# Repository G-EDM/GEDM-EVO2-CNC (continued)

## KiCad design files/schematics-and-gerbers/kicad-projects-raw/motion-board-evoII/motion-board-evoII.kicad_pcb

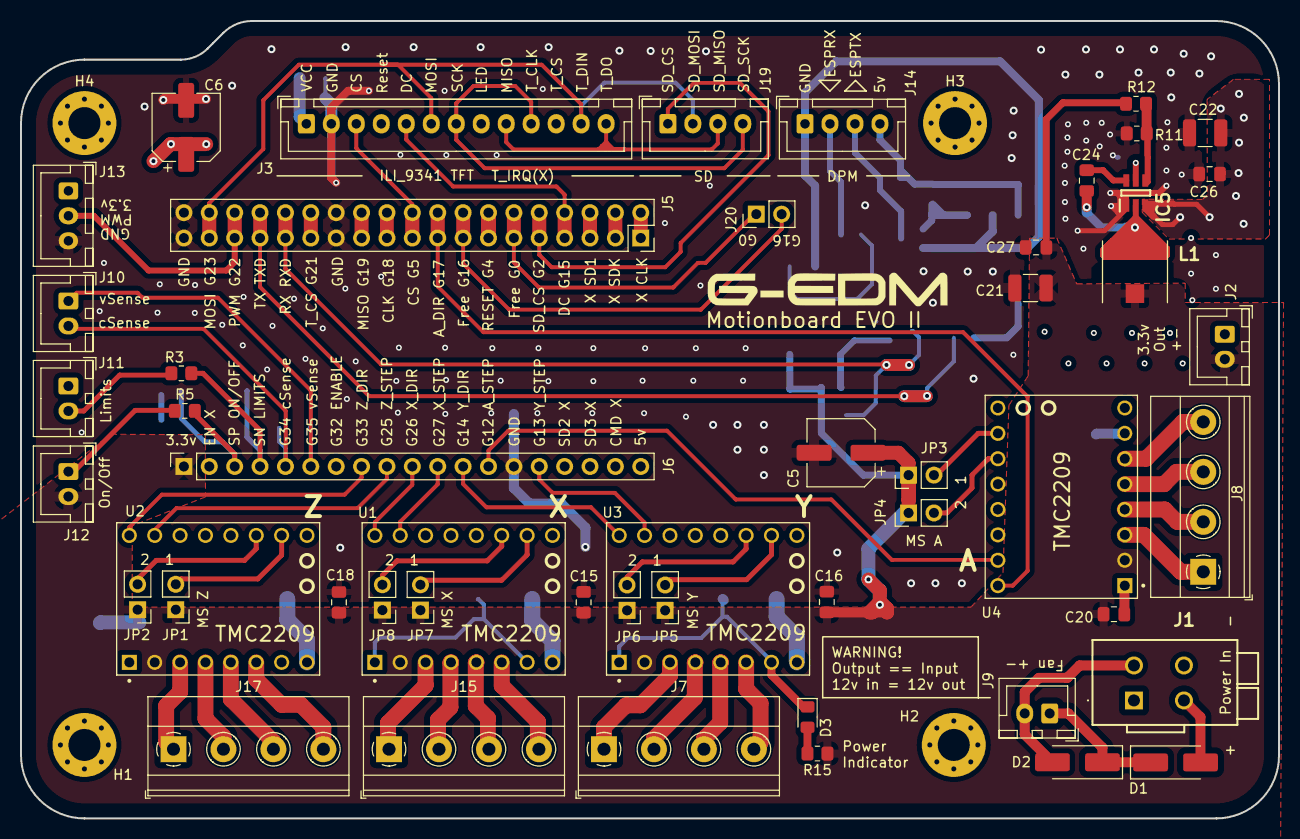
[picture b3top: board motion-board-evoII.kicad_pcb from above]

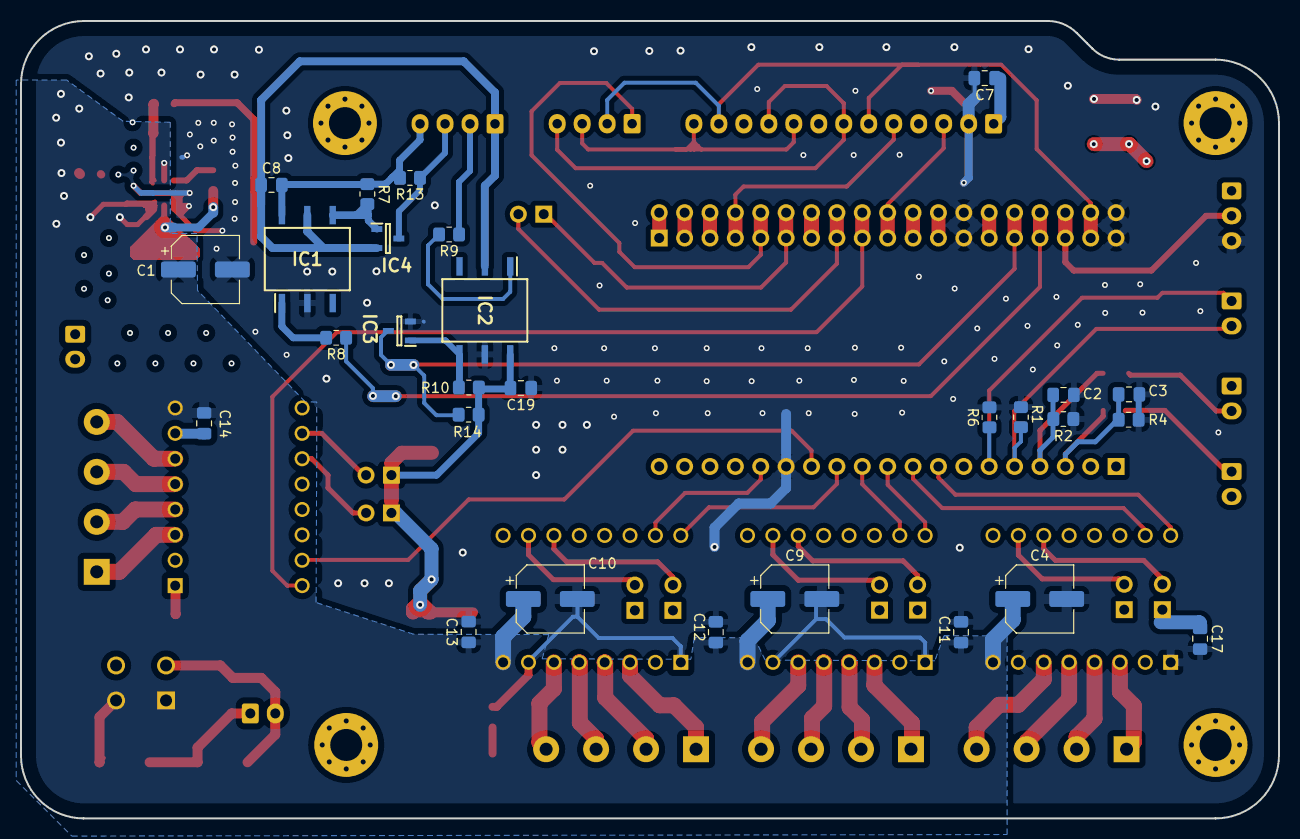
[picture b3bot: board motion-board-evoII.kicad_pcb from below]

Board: 4 copper layers, 125.9 x 79.8 mm, 82 parts (28 on the bottom side), 71 nets.

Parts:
C1, C4, C9, C10: 100uf35v-6.3x7.7mm (EEE-HA1V101XP); CP_Elec_6.3x7.7
C2, C3, C7, C8, C11, C12, C13, C14, C15, C16, C17, C18, C19, C20, C24, C26, C27: 0.1uf-50v-x7r; C_0805_2012Metric_Pad1.18x1.45mm_HandSolder
C5, C6: 220uf16v-6.3x7.7mm (EEE-HA1C221XP); CP_Elec_6.3x7.7
C21: 22uf-16v-X7R (GRM32ER71C226KEA8K); C_1210_3225Metric_Pad1.33x2.70mm_HandSolder
C22: 4.7uf-50v-X7R (GRM32ER71H475KA88L); C_1210_3225Metric_Pad1.33x2.70mm_HandSolder
D1, D2: 60v3ASchottky; D_SMA_Handsoldering
D3: 597-3305-607F; LED_0805_2012Metric_Pad1.15x1.40mm_HandSolder
H1: MountingHole_Pad; MountingHole_3.2mm_M3_Pad_Via
H2, H3, H4: MountingHole; MountingHole_3.2mm_M3_Pad_Via
IC1, IC2: H11L1SR2M_F132; SOT254P916X480-6N
IC3, IC4: MMBT3904; SOT95P240X110-3N
IC5: LMR51420XFDDCR; SOT95P280X110-6N
J1: WAGO 2601-1102; 26011102
J2, J9, J10, J11, J12: JST XHP-2; JST_XH_B2B-XH-A_1x02_P2.50mm_Vertical
J3: JST XHP-13; JST_XH_B13B-XH-A_1x13_P2.50mm_Vertical
J5: 2,54mm pin socket 2x19; PinSocket_2x19_P2.54mm_Vertical
J6: 2,54mm pin socket 1x19; PinSocket_1x19_P2.54mm_Vertical
J7, J8, J15, J17: 35° 4-pole screw terminal ( TE Connectivity 79668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; TerminalBlock_Phoenix_MKDS-1,5-4_1x04_P5.00mm_Horizontal
J13: JST XHP-3; JST_XH_B3B-XH-A_1x03_P2.50mm_Vertical
J14, J19: JST XHP-4; JST_XH_B4B-XH-A_1x04_P2.50mm_Vertical
J20: SDI_T_DIN_SD_MOSI; PinHeader_1x02_P2.54mm_Vertical
JP1, JP2, JP3, JP4, JP5, JP6, JP7, JP8: 1x02 pin header with low profilejumper cap (149-3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; PinHeader_1x02_P2.54mm_Vertical
L1: 7447786008 2.3A 8.2uh; WE-PD_6033_6050_PLASTIC_BASE54
R1, R2, R4, R6: 100k; R_0805_2012Metric_Pad1.20x1.40mm_HandSolder
R3, R5: 1k; R_0805_2012Metric_Pad1.20x1.40mm_HandSolder
R7, R10, R14: 470; R_0805_2012Metric_Pad1.20x1.40mm_HandSolder
R8, R13: E330; R_0805_2012Metric_Pad1.20x1.40mm_HandSolder
R9: E499; R_0805_2012Metric_Pad1.20x1.40mm_HandSolder
R11: 22.1k 1% Würth WRIS-RSKS 560112120026; R_0805_2012Metric_Pad1.20x1.40mm_HandSolder
R12: 100k 1%; R_0805_2012Metric_Pad1.20x1.40mm_HandSolder
R15: 220; R_0805_2012Metric_Pad1.20x1.40mm_HandSolder
U1, U2, U3, U4: TMC2209; MODULE_TMC2209_SILENTSTEPSTICK

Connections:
3.3v+: C5.1, C6.1, C7.1, C15.1, C16.1, C17.1, C18.1, C19.2, C20.1, C21.2, C27.2, IC2.6 (VCC), J2.2, J3.1, J3.8, J6.1, J11.1, J12.2, J13.1, JP1.1 (A), JP2.1 (A), JP3.1 (A), JP4.1 (A), JP5.1 (A), JP6.1 (A), JP7.1 (A), JP8.1 (A), L1.2, R10.1, R12.1, R14.2, R15.1, U1.2 (VIO), U2.2 (VIO), U3.2 (VIO), U4.2 (VIO)
12v+: C1.1, C4.1, C9.1, C10.1, C11.1, C12.1, C13.1, C14.1, C22.2, C26.2, D1.2 (A), IC5.3 (VIN), IC5.5 (EN), J1.1 (1.1), J1.2 (1.2), U1.8 (VM), U2.8 (VM), U3.8 (VM), U4.8 (VM)
CLK: J3.7, J3.10, J5.21, J5.22, J19.4
CS: J3.3, J5.19, J5.20
DC: J3.5, J5.7, J5.8
DPMRXB: IC4.3 (COLLECTOR), J14.3, R13.1
DPMTXB: J14.2, R9.1
GND: C1.2, C2.2, C3.2, C4.2, C5.2, C6.2, C7.2, C9.2, C10.2, C11.2, C12.2, C13.2, C14.2, C15.2, C16.2, C17.2, C18.2, C19.1, C20.2, C21.1, C22.1, C26.1, C27.1, D2.2 (A), D3.1 (K), IC1.2 (CATHODE), IC2.5 (GND), IC3.2 (EMITTER), IC5.1 (GND), J1.3 (2.1), J1.4 (2.2), J2.1, J3.2, J5.25, J5.26, J5.37, J5.38, J6.14, J9.2, J13.3, R1.2, R2.2, R4.2, R6.2, R11.2, U1.1 (GND), U1.7 (GND), U2.1 (GND), U2.7 (GND), U3.1 (GND), U3.7 (GND), U4.1 (GND), U4.7 (GND)
GND5v: C8.1, IC1.5 (GND), IC2.2 (CATHODE), IC4.2 (EMITTER), J14.1
GPIO16: J5.15, J5.16, J20.2
Limit39: C2.1, J6.4, R2.1, R3.2
MOSI: J3.6, J3.12, J5.35, J5.36, J19.2
Miso: J3.9, J3.13, J5.23, J5.24, J19.3
unnamed: D1.1 (K), D2.1 (K), J9.1
unnamed: D3.2 (A), R15.2
unnamed: IC1.1 (ANODE), R8.2
unnamed: IC1.4 (VO), IC4.1 (BASE), R7.2
unnamed: IC2.1 (ANODE), R9.2
unnamed: IC2.4 (VO), IC3.1 (BASE), R10.2
unnamed: C24.1, IC5.6 (CB)
unnamed: IC5.4 (FB), R11.1, R12.2
unnamed: C24.2, IC5.2 (SW), L1.1
unnamed: J5.1, J5.2
unnamed: J5.3, J5.4
unnamed: J5.5, J5.6
unnamed: J7.1, U3.3 (M1B)
unnamed: J7.2, U3.4 (M1A)
unnamed: J7.3, U3.5 (M2A)
unnamed: J7.4, U3.6 (M2B)
unnamed: J8.1, U4.3 (M1B)
unnamed: J8.2, U4.4 (M1A)
unnamed: J8.3, U4.5 (M2A)
unnamed: J8.4, U4.6 (M2B)
unnamed: J11.2, R3.1
unnamed: J12.1, R5.1
unnamed: J15.1, U1.3 (M1B)
unnamed: J15.2, U1.4 (M1A)
unnamed: J15.3, U1.5 (M2A)
unnamed: J15.4, U1.6 (M2B)
unnamed: J17.1, U2.3 (M1B)
unnamed: J17.2, U2.4 (M1A)
unnamed: J17.3, U2.5 (M2A)
unnamed: J17.4, U2.6 (M2B)
PWM: J5.33, J5.34, J13.2
RX(IO3): IC3.3 (COLLECTOR), J5.29, J5.30, R14.1
SD_CS: J5.9, J5.10, J19.1
Start36: C3.1, J6.3, R4.1, R5.2
TX(IO1): J5.31, J5.32, R8.1
T_CS: J3.11, J5.27, J5.28
VCCB: C8.2, IC1.6 (VCC), J14.4, R7.1, R13.2
adir17: J5.17, J5.18, U4.9 (DIR)
ams1: JP3.2 (B), U4.15 (MS1)
ams2: JP4.2 (B), U4.14 (MS2)
astep12: J6.13, U4.10 (STEP)
enable-all: J6.7, U1.16 (~EN), U2.16 (~EN), U3.16 (~EN), U4.16 (~EN)
gpio0: J5.11, J5.12, J20.1
input35: J6.6, J10.1, R6.1
reset: J3.4, J5.13, J5.14
vSense34: J6.5, J10.2, R1.1
xdir: J6.10, U1.9 (DIR)
xms1: JP7.2 (B), U1.15 (MS1)
xms2: JP8.2 (B), U1.14 (MS2)
xstep: J6.11, U1.10 (STEP)
ydir: J6.12, U3.9 (DIR)
yms1: JP5.2 (B), U3.15 (MS1)
yms2: JP6.2 (B), U3.14 (MS2)
ystep: J6.15, U3.10 (STEP)
zdir: J6.8, U2.9 (DIR)
zms1: JP1.2 (B), U2.15 (MS1)
zms2: JP2.2 (B), U2.14 (MS2)
zstep: J6.9, U2.10 (STEP)

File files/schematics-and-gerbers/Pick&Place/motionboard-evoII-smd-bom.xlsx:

| G-EDM Motionboard EVOII – SMD/SMT BOM
Item # | *Designator | *Qty | Manufacturer | *Mfg Part # | Description / Value | *Package/Footprint | Type | Your Instructions / Notes
1 | C2,C3,C7,C8,C11,C12,C13,C14,C15,C16,C17,C18,C19,C20,C24,C26,C27 | 17 | KYOCERA AVX | 08055C104K4T2A | 0.1uf 50v X7R 10% MLCC | 0805 | SMD
2 | C22 | 1 | Murata Electronics | GRM32ER71H475KA88L | 4.7uf 50v X7R 10% MLCC | 1210 | SMD
3 | C21 | 1 | Murata Electronics | GRM32ER71C226KEA8K | 22uf 16v X7R 10% MLCC | 1210 | SMD
4 | C1,C4,C9,C10 | 4 | Panasonic | EEE-HA1V101XP | 100uf 35v 6.3x7.7mm Electrolytic Capacitor | CP_Elec_6.3x7.7 | SMD
5 | C5,C6 | 2 | Panasonic | EEE-HA1C221XP | 220uf 16v 6.3x7.7mm Electrolytic Capacitor | CP_Elec_6.3x7.7 | SMD
6 | R8,R13 | 2 | Vishay / Dale | RCC0805330RFKEA | 330 Ohm 1% 1/4W resistor | 0805 | SMD
7 | R7,R10,R14 | 3 | Vishay / Dale | RCC0805470RFKEA | 470 Ohm 1% 1/4W resistor | 0805 | SMD
8 | R1,R2,R4,R6,R12 | 5 | Würth | 560112120013 | 100 kOhm 1% 1/4W resistor | 0805 | SMD
9 | R9 | 1 | Walsin | MR08X4990FTL | 499 Ohm 1% 1/4W resistor | 0805 | SMD
10 | R3,R5 | 2 | Panasonic | ERJ-T06J102V | 1 kOhm 5% 1/4W resistor | 0805 | SMD
11 | R11 | 1 | Würth | 560112120026 | 22.1 kOhm 1% 1/4W resistor | 0805 | SMD
12 | R15 | 1 | Panasonic | ERJ-T06J221V | 220 Ohm 5% 1/4W resistor | 0805 | SMD
13 | D3 | 1 | Dialight | 597-3305-607F | LED green 10mA 2.1V | 0805 | SMD
14 | D1,D2 | 2 | Vishay General Semiconductor | B360A-E3/61T | 3A 60v Schottky diode | SMA (DO-214AC) | SMD
15 | L1 | 1 | Würth | 7447786008 | 8.2uH 2.3A DCR=80mOhms Shielded Power Choke Coil | WE-PD_6033_6050_PLASTIC_BASE54 | SMD
16 | IC5 | 1 | Texas Instruments | LMR51420XFDDCR | SIMPLE SWITCHER power converter 4.5-V-36-V 2A | SOT-23-6 | SMD
17 | IC3,IC4 | 2 | Diotec Semiconductor | MMBT3904 | NPN BJT transistor 40V 200mA | SOT-23-3 | SMD
18 | IC1,IC2 | 2 | onsemi / Fairchild | H11L1SR2M | Logic Schmitt trigger optocoupler | SMD-6 PDIP6 | SMD

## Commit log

2024-04-14 Rename readme.md5 to readme.md
2024-04-14 Rename partlist-and-instructions.md5 to partlist-and-instructions.md
2024-06-12 Add files via upload
    3/4" water outlet for two M10 fittings to connect the wire module.
2024-06-12 main wire module v4 - enlarged pockets for slide bushings
    The pockets for the v1-3 wire module are very tight and getting the slide bushings in required heavy heating and was just not worth the trouble. Enlarged the pockets a little for v4.
2024-06-13 Small changes on some screw pockets and bigger holes for the slide bushings
2024-06-30 Added current contact mount
2024-08-08 Added tech drawings for the portal plate
2024-08-13 Added schmeatics for the pulseboard EVO²
    Check the readme first. It is just the pulseboards schematics without the sensing circuit.
2024-08-13 Rename pulseboard-evo-cube-schematics.pdf to pulseboard-evo-cube-schematics.pdf
2024-08-13 Rename readme.md to readme.md
2024-08-27 Rename files/readme.md to files/wiring/readme.md
2024-08-27 Added motionboard schematics
2024-09-09 uploaded all gerber files, schematics and kicad projects
2024-09-30 Rename files/schematics-and-gerbers/motion-board-evoII.csv to files/schematics-and-gerbers/BOMs/motion-board-evoII.csv
2024-10-09 A little stronger
2024-11-12 New panel
    Slightly changed the panel to add a switch on the side.
2025-01-15 Rename 29-6N137S.png to 29-6N137S-warning-dotmarking-on-the-ic-is-wrong.png
